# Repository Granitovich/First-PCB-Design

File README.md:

# First PCB Design: STM32G0B1KET6 Custom Board

A custom PCB design built around the **STM32G0B1KET6** microcontroller. This project contains a complete hardware design for a minimal development board featuring power management, debugging interfaces, and a directly mounted TFT display.

## 📌 Features

* **Microcontroller:** STM32G0B1KET6 (ARM Cortex-M0+, 512 KB Flash, 144 KB RAM, up to 64 MHz).
* **Display Interface:** Dedicated pinout and footprint for mounting a TFT LCD module directly on top of the PCB.
* **Power Supply:** 
  * Linear voltage regulator (LDO) to step down input voltage to +3.3V.
  * Decoupling and bulk capacitors for stable operation and MCU noise suppression.
* **Programming & Debugging:** Standard SWD (Serial Wire Debug) header for ST-LINK / J-Link programmers.
* **System Essentials:**
  * Reset circuit with an onboard tactile button and debouncing.
  * Status LEDs for power indication

## 📁 Repository Structure

```text
├── # Schematics, PCB layout files, and KiCad/Altium project source
├── production/        # Production-ready Gerber files, drill files, and pick-and-place (CPL)
├── BOM/               # Bill of Materials (components list with manufacturer part numbers)
└── README.md          # Project documentation

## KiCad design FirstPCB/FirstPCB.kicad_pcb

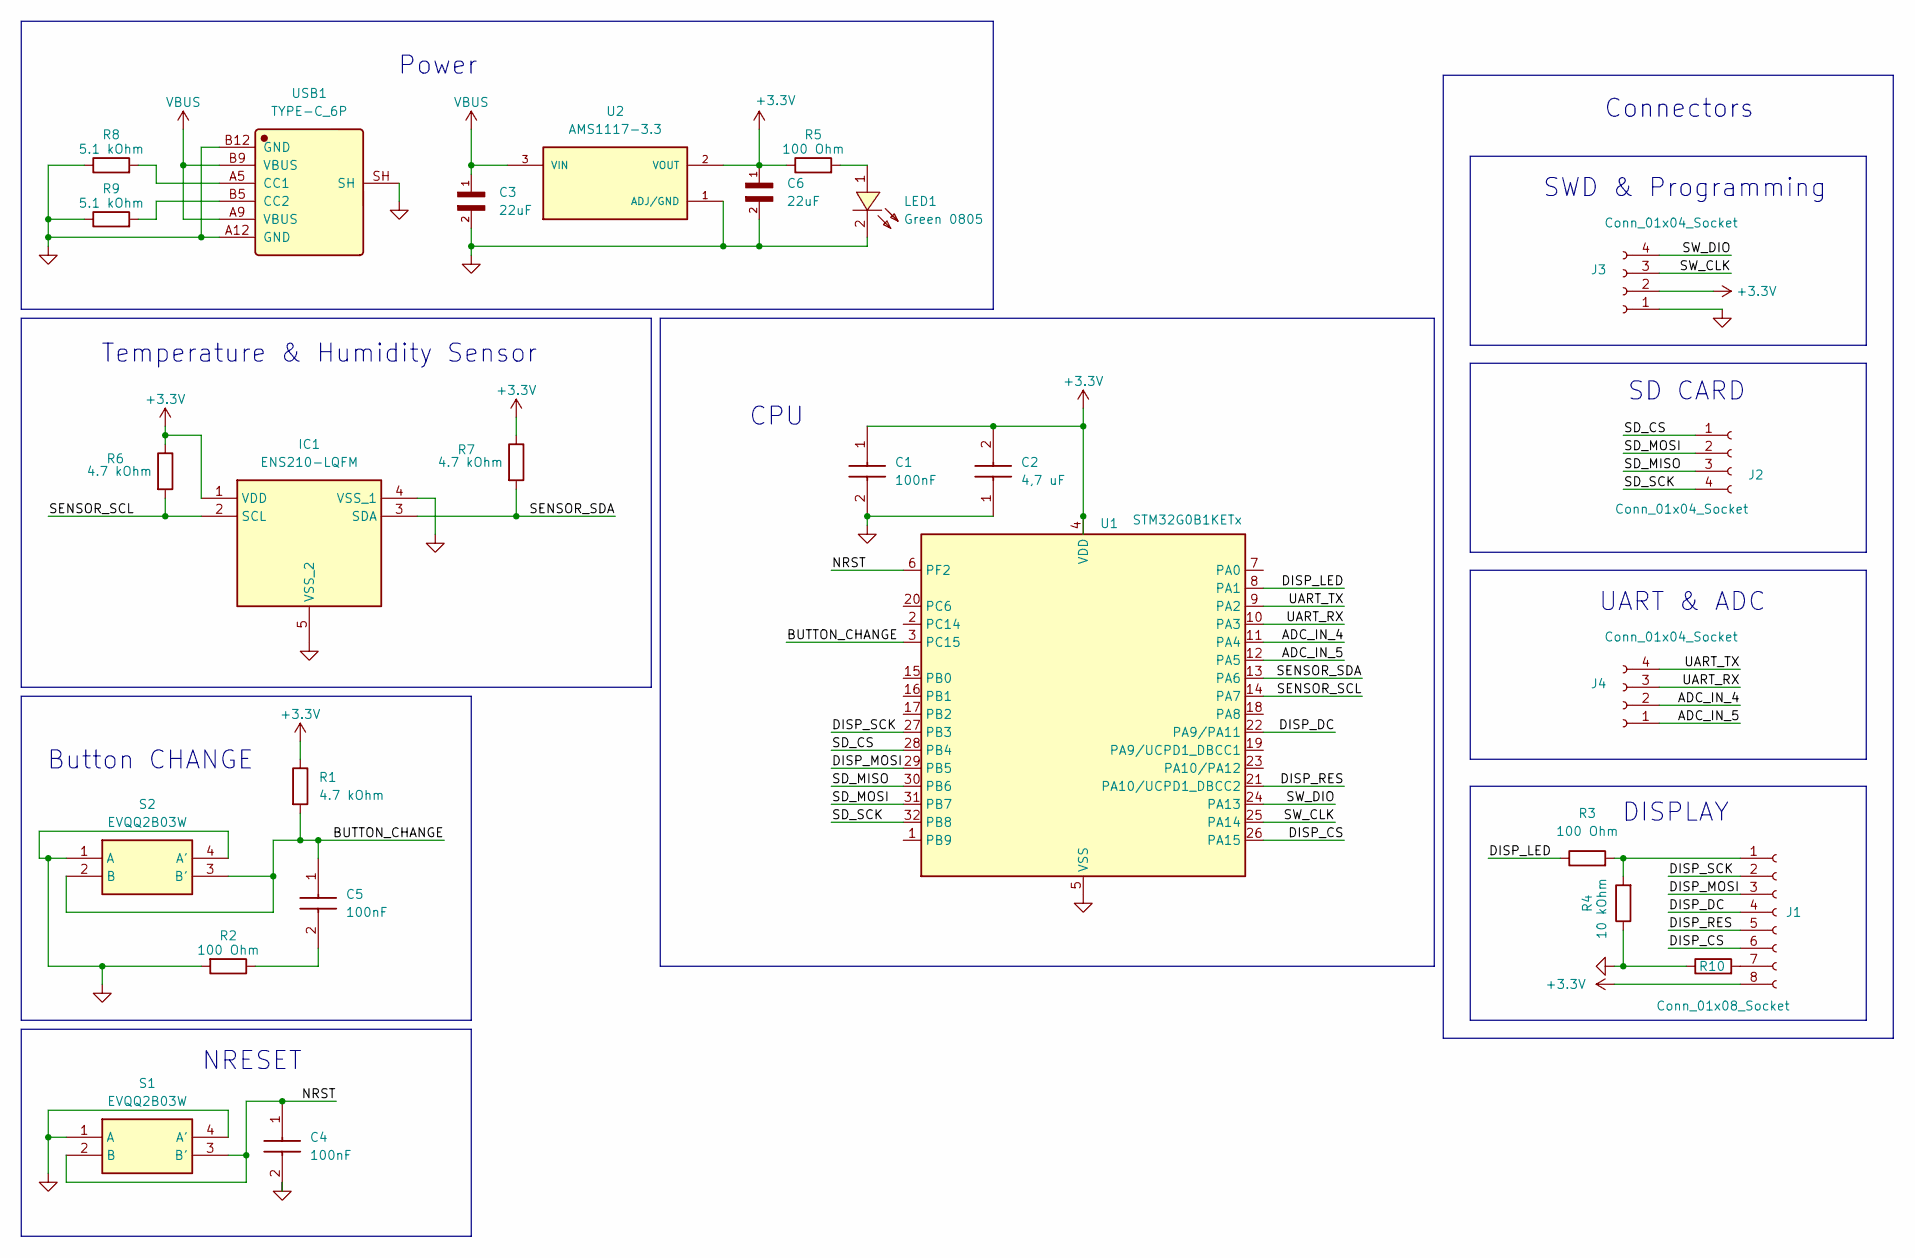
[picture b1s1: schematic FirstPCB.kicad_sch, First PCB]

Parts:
C1, C4, C5: 100nF; CAPC2012X95N; Manufacturer_Part_Number CL21B104KBCNNNC; Mouser Part Number 187-CL21B104KBCNNNC
C2: 4,7 uF; CAPC2012X140N; Manufacturer_Part_Number CL21A475KAQNNNE; Mouser Part Number 187-CL21A475KAQNNNE
C3, C6: 22uF; CAPC2012X140N
IC1: ENS210-LQFM; SON95P200X200X80-5N; Manufacturer_Part_Number ENS210-LQFM; Mouser Part Number 985-ENS210-LQFM
J1: Conn_01x08_Socket; PinSocket_1x08_P2.54mm_Vertical
J2: Conn_01x04_Socket; PinSocket_1x04_P2.54mm_Vertical
J3, J4: Conn_01x04_Socket; PinHeader_1x04_P2.54mm_Horizontal
LED1: Green 0805; RESC3115X65N; MPN KT-0805YG; LCSC Part C2292
R1, R6, R7: 4.7 kOhm; R_0805_2012Metric
R2, R3, R5: 100 Ohm; R_0805_2012Metric
R4: 10 kOhm; R_0805_2012Metric
R8, R9: 5.1 kOhm; R_0805_2012Metric
R10: 1 Ohm; R_0805_2012Metric
S1, S2: EVQQ2B03W; EVQQ2; Manufacturer_Part_Number EVQQ2B03W
U1: STM32G0B1KETx; LQFP-32_7x7mm_P0.8mm
U2: AMS1117-3.3; SOT-223-3_TabPin2; PARTREV NA
USB1: TYPE-C_6P; USB_C_Receptacle_GCT_USB4135-GF-A_6P_TopMnt_Horizontal; Manufacturer Part TYPE-C 6P; LCSC C456012

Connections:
+3.3V: C1.1, C2.2, C6.1, IC1.1 (VDD), J1.8, J3.2, R1.1, R5.1, R6.1, R7.1, U1.4 (VDD), U2.2 (VOUT)
/ADC_IN_4: J4.2, U1.11 (PA4)
/ADC_IN_5: J4.1, U1.12 (PA5)
/BUTTON_CHANGE: C5.1, R1.2, S2.2 (B), S2.3 (B'), U1.3 (PC15)
/DISP_CS: J1.6, U1.26 (PA15)
/DISP_DC: J1.4, U1.22 (PA9/PA11)
/DISP_LED: R3.1, U1.8 (PA1)
/DISP_MOSI: J1.3, U1.29 (PB5)
/DISP_RES: J1.5, U1.21 (PA10/UCPD1_DBCC2)
/DISP_SCK: J1.2, U1.27 (PB3)
/NRST: C4.1, S1.2 (B), S1.3 (B'), U1.6 (PF2)
/SD_CS: J2.1, U1.28 (PB4)
/SD_MISO: J2.3, U1.30 (PB6)
/SD_MOSI: J2.2, U1.31 (PB7)
/SD_SCK: J2.4, U1.32 (PB8)
/SENSOR_SCL: IC1.2 (SCL), R6.2, U1.14 (PA7)
/SENSOR_SDA: IC1.3 (SDA), R7.2, U1.13 (PA6)
/SW_CLK: J3.3, U1.25 (PA14)
/SW_DIO: J3.4, U1.24 (PA13)
/UART_RX: J4.3, U1.10 (PA3)
/UART_TX: J4.4, U1.9 (PA2)
GND: C1.2, C2.1, C3.2, C4.2, C6.2, IC1.4 (VSS_1), IC1.5 (VSS_2), J3.1, LED1.2, R2.2, R4.1, R8.1, R9.1, R10.1, S1.1 (A), S1.4 (A'), S2.1 (A), S2.4 (A'), U1.5 (VSS), U2.1 (ADJ/GND), USB1.A12 (GND), USB1.B12 (GND), USB1.SH
unnamed: C5.2, R2.1
unnamed: J1.1, R3.2, R4.2
unnamed: J1.7, R10.2
unnamed: LED1.1, R5.2
unnamed: R8.2, USB1.A5 (CC1)
unnamed: R9.2, USB1.B5 (CC2)
VBUS: C3.1, U2.3 (VIN), USB1.A9 (VBUS), USB1.B9 (VBUS)

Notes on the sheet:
Temperature & Humidity Sensor
Button CHANGE
CPU
Connectors
DISPLAY
SD CARD
NRESET
UART & ADC
SWD & Programming
Power

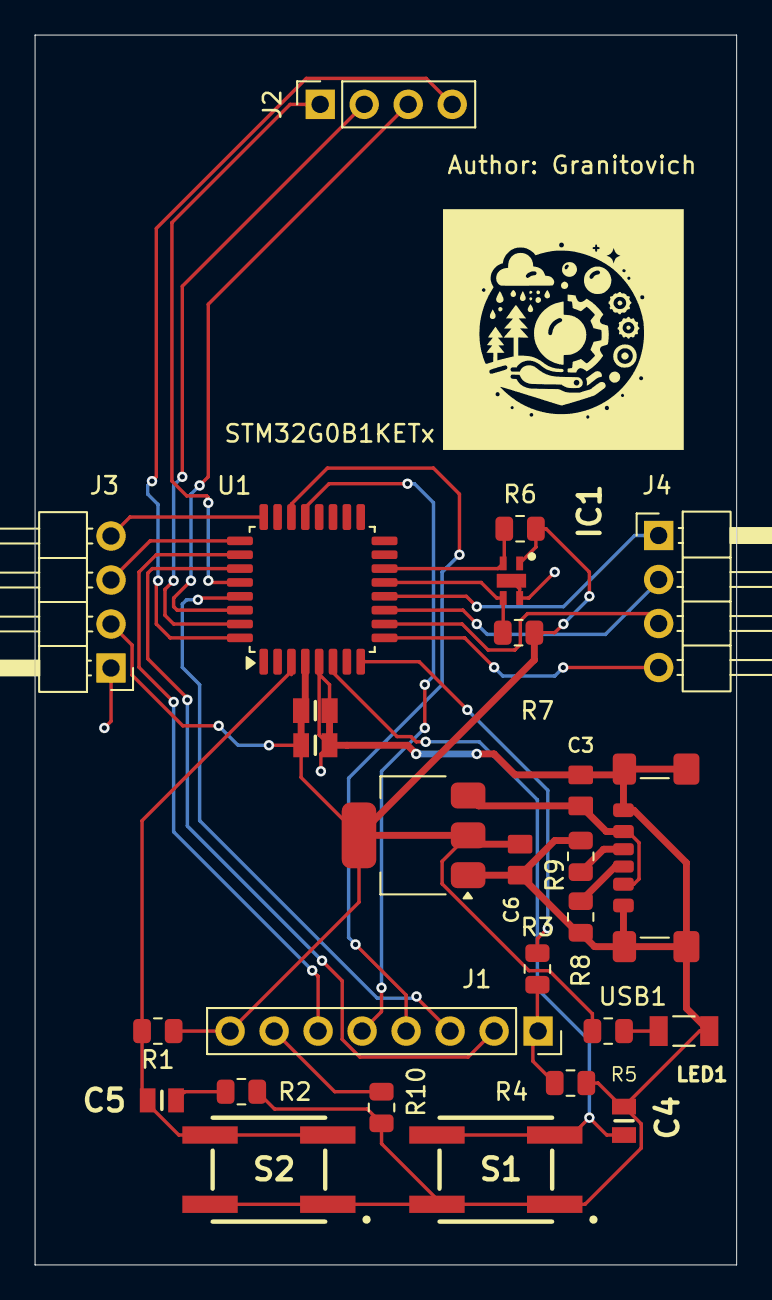
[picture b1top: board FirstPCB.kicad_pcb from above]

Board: 2 copper layers, 40.5 x 71.0 mm, 27 parts (0 on the bottom side), 29 nets.
